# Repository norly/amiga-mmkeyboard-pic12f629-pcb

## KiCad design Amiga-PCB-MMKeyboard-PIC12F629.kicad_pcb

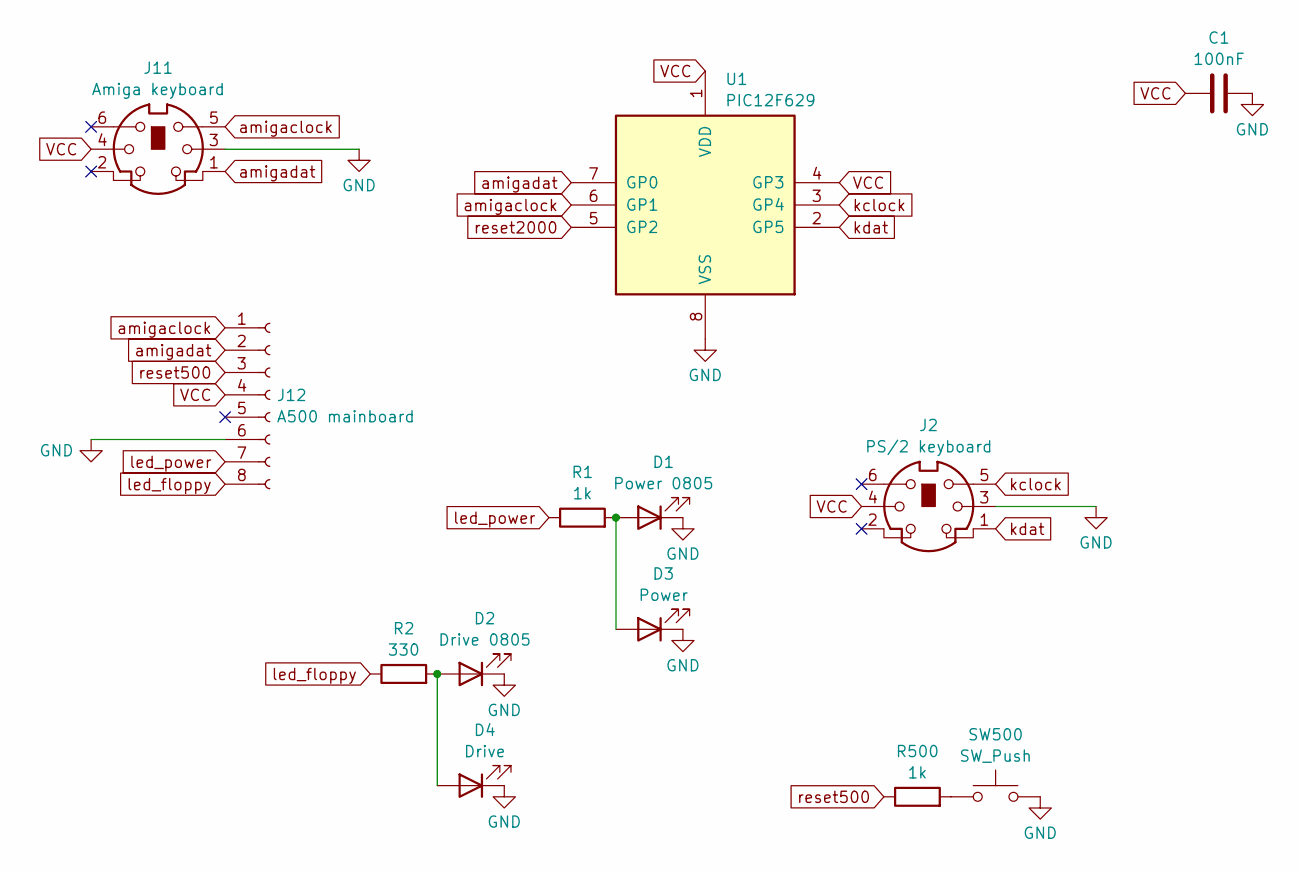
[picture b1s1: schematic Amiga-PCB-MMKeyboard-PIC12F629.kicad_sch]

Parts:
C1: 100nF; C_0805_2012Metric_Pad1.18x1.45mm_HandSolder; JLCPCB C49678
D1: Power 0805; LED_0805_2012Metric_Pad1.15x1.40mm_HandSolder; JLCPCB C2297
D2: Drive 0805; LED_0805_2012Metric_Pad1.15x1.40mm_HandSolder; JLCPCB C2296
D3: Power; LED_D3.0mm
D4: Drive; LED_D3.0mm
J2: PS/2 keyboard; Mini-DIN-6_PS2-Keyboard-Socket_Connfly_DS1093-01-PN60; LCSC C77848
J11: Amiga keyboard; Mini-DIN-6_PS2-Keyboard-Socket_Connfly_DS1093-01-PN60; LCSC C77848
J12: A500 mainboard; PinSocket_1x08_P2.54mm_Vertical; LCSC C2685213
R1, R500: 1k; R_0805_2012Metric_Pad1.20x1.40mm_HandSolder; JLCPCB C17513
R2: 330; R_0805_2012Metric_Pad1.20x1.40mm_HandSolder; JLCPCB C17630
SW500: SW_Push; PinHeader_1x02_P2.54mm_Horizontal; LCSC C7501290
U1: PIC12F629; DIP-8_W7.62mm; LCSC C72124

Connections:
GND: C1.2, D1.1 (K), D2.1 (K), D3.1 (K), D4.1 (K), J2.3, J11.3, J12.6, SW500.1, U1.8 (VSS)
unnamed: D1.2 (A), D3.2 (A), R1.2
unnamed: D2.2 (A), D4.2 (A), R2.2
unnamed: R500.2, SW500.2
VCC: C1.1, J2.4, J11.4, J12.4, U1.1 (VDD), U1.4 (GP3)
amigaclock: J11.5, J12.1, U1.6 (GP1)
amigadat: J11.1, J12.2, U1.7 (GP0)
kclock: J2.5, U1.3 (GP4)
kdat: J2.1, U1.2 (GP5)
led_floppy: J12.8, R2.1
led_power: J12.7, R1.1
reset500: J12.3, R500.1
reset2000: U1.5 (GP2)

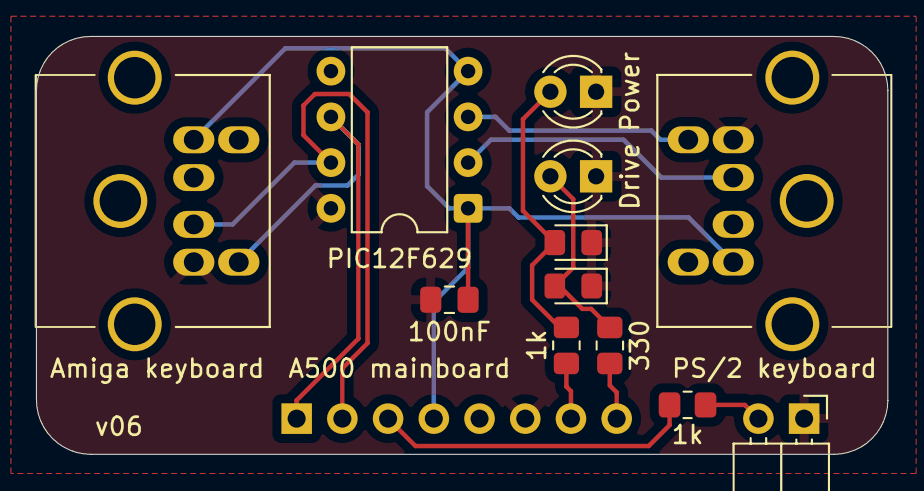
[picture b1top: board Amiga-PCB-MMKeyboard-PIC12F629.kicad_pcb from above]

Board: 2 copper layers, 47.3 x 23.2 mm, 13 parts (1 on the bottom side), 12 nets.

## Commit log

2024-01-05 Add .gitignore
2024-01-14 v02
    - Update PS/2 socket footprint
    - Print "values" on silkscreen
    - Add 100 nF for PIC
    - Shorten "values"
    - Move things to the left for more space and to balance the look
2024-01-25 v03: Fix mirrored pin numbering on PS/2 (Mini DIN 6) connectors
    The previous versions couldn't actually work due to a mistake in the
    Mini DIN 6 connector footprint.
2024-02-15 LICENSE: CC0
2024-03-06 v04: Change resistors to 470 Ohm, late A500 LED colours
    200 Ohm are the original value seen on an A500 keyboard, but with modern
    0805 LEDs this ends up too bright.
    The JLCPCB/LCSC part numbers for the SMD LEDs are now:
    - Power: green
    - Drive: yellow
2024-03-10 Add Reichelt order numbers
2024-05-31 v05: Fix A500 interface, add A500 reset button
    The A500 part was untested.
    - data/clock were swapped
    - reset was wrongly connected to the PIC
    Added a jumper to reset an A500.
2025-06-15 KiCad 9.0 and add local copy of Mini-DIN-6 socket footprint
2025-06-15 v06: Sane LED resistor values depending on the LED's properties
